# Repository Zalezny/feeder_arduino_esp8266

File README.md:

# Automated Feeder

An Automated Feeder designed for guinea pigs (and adaptable for other animals). It operates using an ESP8266 microcontroller. As part of the project, a rotating screw mechanism was 3D printed to dispense the feed.

## Scheme (Eagle)

## Board (Eagle)

## Parts

- Processor: ESP8266 WiFi
- LCD 4x20 green LCD-01136
- Clock RTC: MSX RTC DS1307
- Stepper motor: 28BYJ-48
- Power: Impulse Power Supply 3-12V/1.2A (for this project 5V)
- Mechanism: Rotating Screw (Printer 3D)

## How it works 

When you connect the feeder to power, the program will start counting down, and when it reaches zero, the feeder will begin dispensing feed.

ESP8266 is configured to REST Server with endpoints like /setTimer - set hour, minute, second or /setState - set pause, resume or restart

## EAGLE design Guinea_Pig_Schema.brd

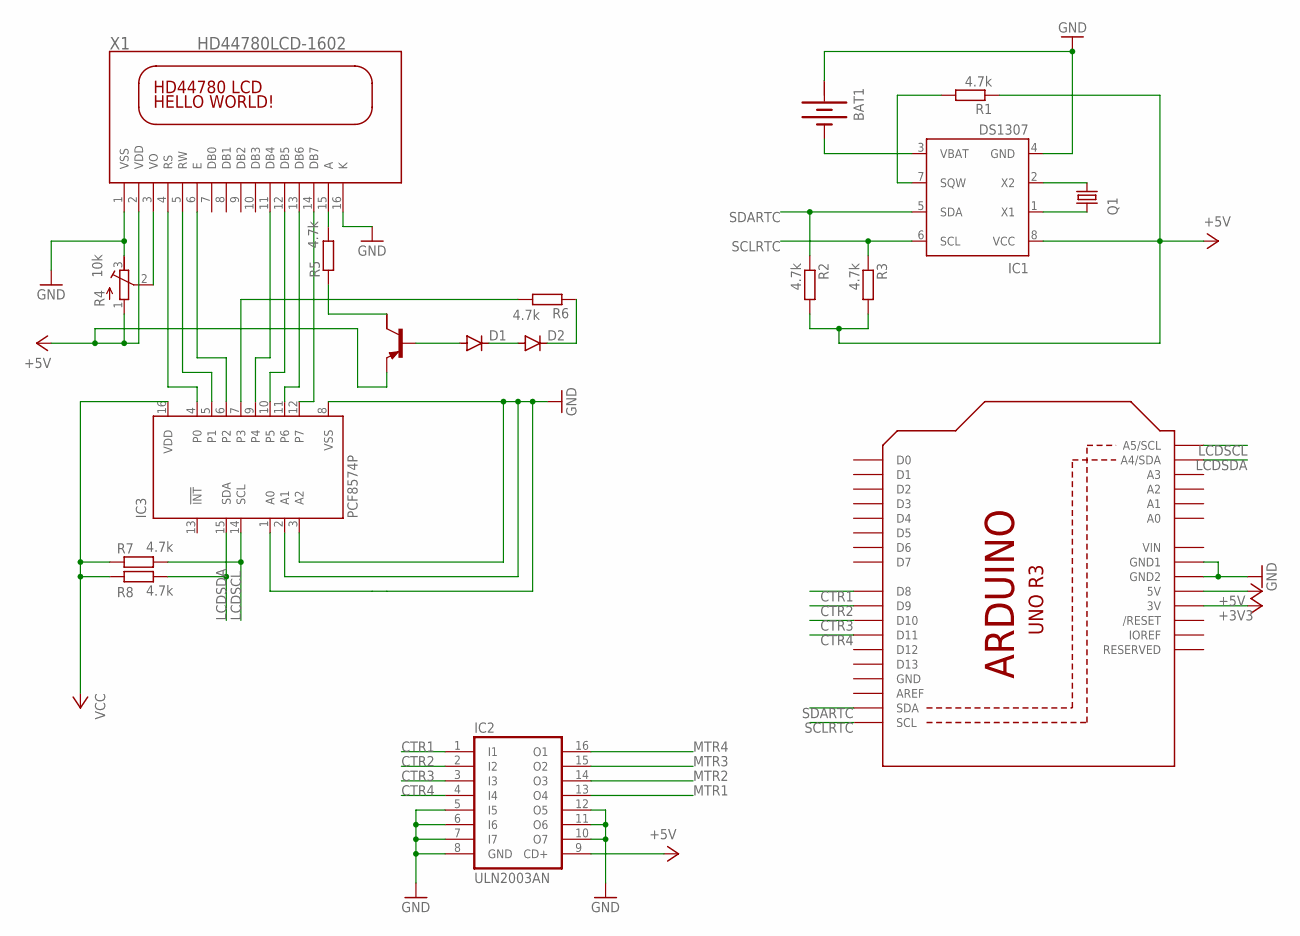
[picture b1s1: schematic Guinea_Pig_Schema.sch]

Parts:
BAT1: BATTERY
D1, D2: DIODE-DO-214AC; DO-214AC
IC1: DS1307; DIL08
IC2: ULN2003AN; DIL16
IC3: PCF8574P; DIL16
Q1: CRYSTAL68SMX; 86SMX
Q2: PNP-TRANSISTIOR-2COLSOT89; SOT89
R1, R2, R3, R5, R6, R7, R8: 4.7k; R1206
R4: 10k; RTRIM3224X
U1: ARDUINOR3-BPLACE
X1: HD44780LCD-1602; LCD1602

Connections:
+: BAT1.+@1 (+)
+3V3: U1.3V
+5V: IC2.9 (CD+), U1.5V
CTR1: IC2.1 (I1), U1.D8
CTR2: IC2.2 (I2), U1.D9
CTR3: IC2.3 (I3), U1.D10
CTR4: IC2.4 (I4), U1.D11
GND: BAT1.+, IC1.4 (GND), IC2.5 (I5), IC2.6 (I6), IC2.7 (I7), IC2.8 (GND), IC2.10 (O7), IC2.11 (O6), IC2.12 (O5), IC3.1 (A0), IC3.2 (A1), IC3.3 (A2), IC3.8 (VSS), R4.3 (E), U1.GND, U1.GND1, U1.GND2, X1.1 (VSS), X1.16 (K)
LCDSCL: IC3.14 (SCL), R7.2, U1.A5 (A5/SCL)
LCDSDA: IC3.15 (SDA), R8.2, U1.A4 (A4/SDA)
MTR1: IC2.13 (O4)
MTR2: IC2.14 (O3)
MTR3: IC2.15 (O2)
MTR4: IC2.16 (O1)
unnamed: IC1.2 (X2), Q1.1
unnamed: IC1.1 (X1), Q1.4 (2)
unnamed: BAT1.-, IC1.3 (VBAT)
unnamed: R4.2 (S), X1.3 (VO)
unnamed: IC1.7 (SQW), R1.2
unnamed: IC3.4 (P0), X1.4 (RS)
unnamed: IC3.5 (P1), X1.5 (RW)
unnamed: IC3.6 (P2), X1.6 (E)
unnamed: IC3.9 (P4), X1.11 (DB4)
unnamed: IC3.10 (P5), X1.12 (DB5)
unnamed: IC3.11 (P6), X1.13 (DB6)
unnamed: IC3.12 (P7), X1.14 (DB7)
unnamed: R5.2, X1.15 (A)
unnamed: Q2.2 (C), R5.1
unnamed: IC3.7 (P3), R6.2
unnamed: D1.A, Q2.1 (B)
unnamed: D1.C, D2.A
unnamed: D2.C, R6.1
SCLRTC: IC1.6 (SCL), R3.1, U1.SCL
SDARTC: IC1.5 (SDA), R2.1, U1.SDA
VCC: IC1.8 (VCC), IC3.16 (VDD), R1.1, R2.2, R3.2, R7.1, R8.1
VDD: Q2.3 (E), R4.1 (A), X1.2 (VDD)
VIN: U1.VIN

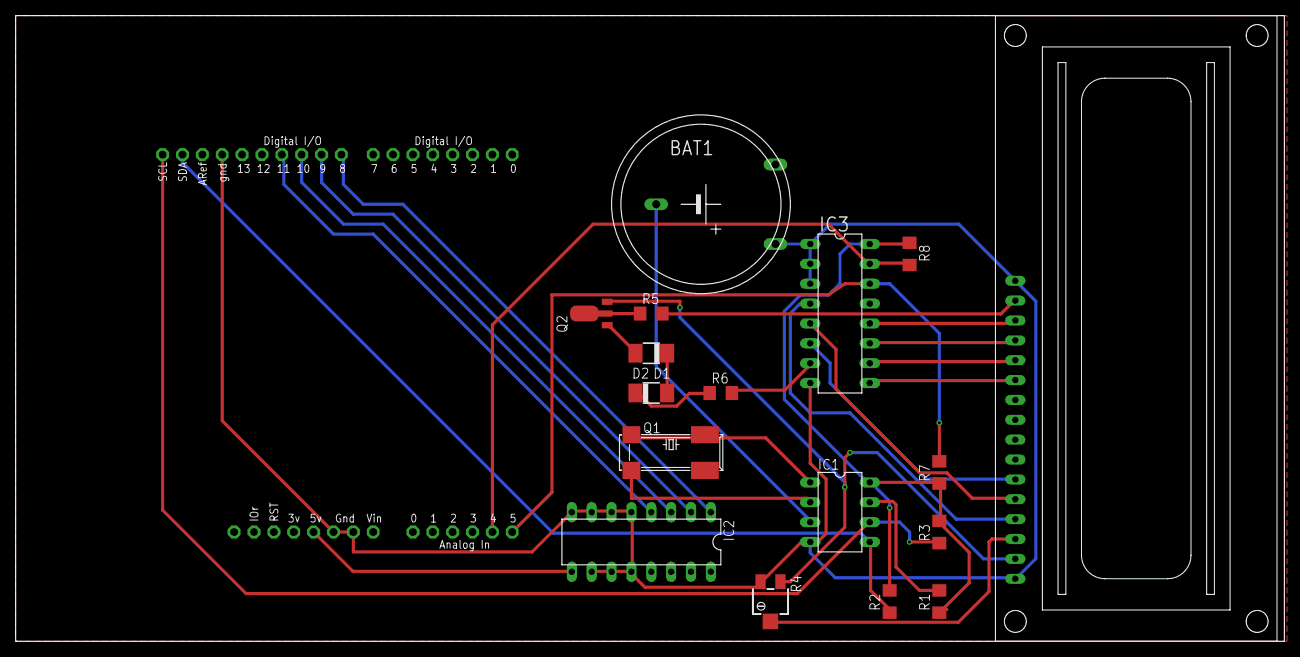
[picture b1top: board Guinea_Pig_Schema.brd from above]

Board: 2 copper layers, 162.2 x 80.0 mm, 18 parts (0 on the bottom side), 30 nets.

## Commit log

2024-02-06 project with local working
2024-02-06 feeder schema and board
2024-02-07 clean code for Feeder and Timer
2024-02-07 gitignore
2024-02-08 fix rtc and add init settings ip
2024-02-09 init rest and create example GET
2024-02-09 Create post method for time and handle errors
2024-02-10 added to post init hour,minutes and seconds
2024-02-11 fix of parse to int and long. Fix clock
2024-02-11 add setState endpoint
2024-02-18 fix pause
